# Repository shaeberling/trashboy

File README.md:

<p align="center">
  <em>A pocketable TRS-80 Model III/IV. Yes, really.</em>
</p>

## What is this?

A handheld **TRS-80 Model III / IV emulator** running on an ESP32-S3 board with a 640×480 RGB LCD.

It runs at original-hardware clock speed — 2.028 MHz for Model III, 4.055 MHz for Model IV — synchronised to wall-clock time so games play at their original speed. The 8 × 12 (M3) and 8 × 10 (M4) glyphs are blitted into an LVGL canvas with 90° rotation, so the portrait panel reads as a landscape Model III screen.

## Hardware

| Part | Role |
|------|------|
| **ESP32-S3** with 8 MB octal PSRAM | Runs the emulator, LVGL UI, BT, Wi-Fi, and a 16-bit RGB LCD bus simultaneously. |
| **ST7701S 480×640 RGB LCD** | Drawn as 640×480 landscape via software rotation in the LVGL flush callback. |
| **GT911 capacitive touch** | I²C; used for the boot-time input-test screen. |
| **TCA9554PWR I/O expander @ 0x20** | On-board: LCD CS, backlight enable, buzzer reset, etc. |
| **MCP23017 I/O expander @ 0x21** | Physical board buttons. Interrupt-driven via INTA → GPIO4. |
| **Bluetooth HID keyboard** | Any generic BT keyboard. Pairing persists in NVS. |
| **Buzzer** | LEDC PWM on GPIO 6 (shared with the LCD backlight channel). |

## Software stack

- **ESP-IDF** — Official ESP32 software stack
- **LVGL v9.1** in `LV_DISPLAY_RENDER_MODE_PARTIAL` with software rotation done inside the flush callback (the panel has no hardware rotation, and `lv_display_set_rotation` alone only swaps reported dimensions). An adaptive flush callback skips the rotation entirely when the emulator is running, since its TRSCanvas pre-rotates glyphs into an unrotated buffer.
- **libz80** Z80 emulation core in `components/ptrs/`, derived from `apuder/pTRS-80`.
- **RetroStore C SDK** (`components/retrostore-c-sdk/`, git submodule) for fetching downloadable game media. HTTP and decode buffers live in PSRAM to keep internal SRAM available for BT/Wi-Fi coexistence working memory.
- **esp-hid** wrapping BT Classic + BLE for the keyboard host.
- **TRS-IO / TRS-LIB** (`components/trs-io/`, `components/trs-lib/`) for on-screen menus, the F5 settings UI, and TRS-80 system I/O glue.

Want the full picture? See [`firmware/ARCHITECTURE.md`](firmware/ARCHITECTURE.md) — boot sequence, task layout, the rotation handoff between splash and emulator, memory placement rules, and lessons-learned annotations.

## Build & flash

```bash
# Once per shell session:
source ~/.espressif/tools/activate_idf_v6.0.1.sh

cd firmware
idf.py set-target esp32s3        # only the first time
idf.py build
idf.py -p /dev/ttyACM0 flash monitor
```

On WSL2, the USB device routing is its own little adventure — see [`firmware/wsl.md`](firmware/wsl.md).

## Repo layout

```
.
├── assets/         Artwork (logo PNGs)
└── firmware/       ESP-IDF project — the action lives here
    ├── main/         app_main, LVGL UI, splash, Wi-Fi setup,
    │                 RetroStore browser, MCP23017 buttons, input test
    ├── components/   Z80 core, TRS-80 emulator, BT keyboard,
    │                 RetroStore SDK, TRS-IO, TRS-LIB
    ├── scripts/      Serial logger, asset rotation helpers
    ├── ARCHITECTURE.md
    └── wsl.md
```

## Status

Active development on the `lvgl9` branch. Recent direction: ESP-IDF v6 migration, MCP23017 board buttons over IRQs, GT911 touch driver, RetroStore game launching with PSRAM-backed buffers, an adaptive flush callback for the LVGL pipeline.

---

<sub>Not affiliated with Tandy or Radio Shack. The TRS-80 trademark belongs to whoever owns it now.</sub>

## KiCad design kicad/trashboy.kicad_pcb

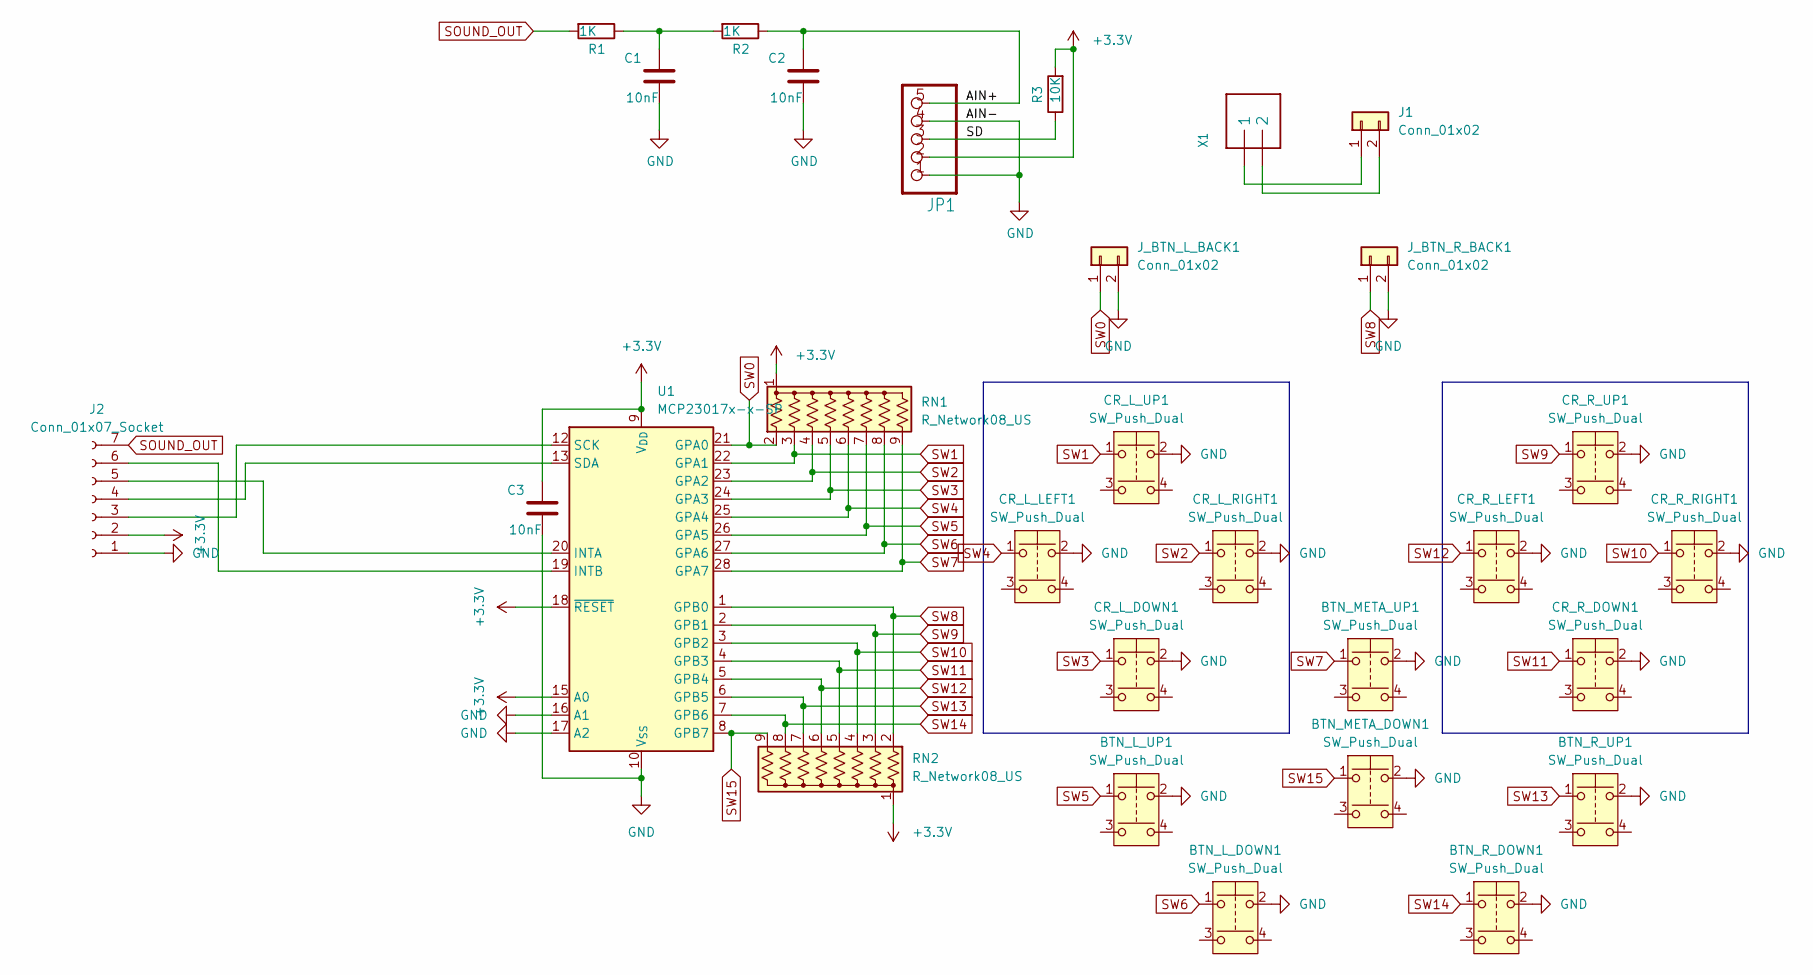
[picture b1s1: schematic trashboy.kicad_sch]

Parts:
BTN_L_DOWN1: SW_Push_Dual; SW_Push_Silicone_8x5mm
BTN_L_UP1: SW_Push_Dual; SW_Push_Silicone_8x5mm
BTN_META_DOWN1: SW_Push_Dual; SW_Push_Silicone_8x5mm
BTN_META_UP1: SW_Push_Dual; SW_Push_Silicone_8x5mm
BTN_R_DOWN1: SW_Push_Dual; SW_Push_Silicone_8x5mm
BTN_R_UP1: SW_Push_Dual; SW_Push_Silicone_8x5mm
C1, C2, C3: 10nF; C_0805_2012Metric_Pad1.18x1.45mm_HandSolder
CR_L_DOWN1: SW_Push_Dual; SW_Push_Silicone_8x5mm
CR_L_LEFT1: SW_Push_Dual; SW_Push_Silicone_8x5mm
CR_L_RIGHT1: SW_Push_Dual; SW_Push_Silicone_8x5mm
CR_L_UP1: SW_Push_Dual; SW_Push_Silicone_8x5mm
CR_R_DOWN1: SW_Push_Dual; SW_Push_Silicone_8x5mm
CR_R_LEFT1: SW_Push_Dual; SW_Push_Silicone_8x5mm
CR_R_RIGHT1: SW_Push_Dual; SW_Push_Silicone_8x5mm
CR_R_UP1: SW_Push_Dual; SW_Push_Silicone_8x5mm
J1: Conn_01x02; PinHeader_1x02_P2.54mm_Vertical
J2: Conn_01x07_Socket; PinHeader_1x07_P2.54mm_Vertical
JP1: HEADER-1X570MIL; 1X05_ROUND_70
J_BTN_L_BACK1: Conn_01x02; PinHeader_1x02_P2.54mm_Vertical
J_BTN_R_BACK1: Conn_01x02; PinHeader_1x02_P2.54mm_Vertical
R1, R2: 1K; R_0805_2012Metric_Pad1.20x1.40mm_HandSolder
R3: 10K; R_0805_2012Metric_Pad1.20x1.40mm_HandSolder
RN1, RN2: R_Network08_US; R_Array_SIP9
U1: MCP23017x-x-SP; DIP-28_W7.62mm
X1: TERMBLOCK_1X2; TERMBLOCK_1X2-3.5MM

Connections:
+3.3V: C3.1, J2.2, JP1.2, R3.2, RN1.1 (common), RN2.1 (common), U1.9 (V_{DD}), U1.15 (A0), U1.18 (~RESET)
/AIN+: C2.1, JP1.5, R2.1
/SD: JP1.3, R3.1
GND: BTN_L_DOWN1.2, BTN_L_UP1.2, BTN_META_DOWN1.2, BTN_META_UP1.2, BTN_R_DOWN1.2, BTN_R_UP1.2, C1.2, C2.2, C3.2, CR_L_DOWN1.2, CR_L_LEFT1.2, CR_L_RIGHT1.2, CR_L_UP1.2, CR_R_DOWN1.2, CR_R_LEFT1.2, CR_R_RIGHT1.2, CR_R_UP1.2, J2.1, JP1.1, JP1.4, J_BTN_L_BACK1.2, J_BTN_R_BACK1.2, U1.10 (V_{SS}), U1.16 (A1), U1.17 (A2)
unnamed: C1.1, R1.1, R2.2
unnamed: J1.1, X1.1
unnamed: J1.2, X1.2
unnamed: J2.3, U1.12 (SCK)
unnamed: J2.4, U1.13 (SDA)
unnamed: J2.5, U1.20 (INTA)
unnamed: J2.6, U1.19 (INTB)
SOUND_OUT: J2.7, R1.2
SW0: J_BTN_L_BACK1.1, RN1.2 (R1), U1.21 (GPA0)
SW1: CR_L_UP1.1, RN1.3 (R2), U1.22 (GPA1)
SW2: CR_L_RIGHT1.1, RN1.4 (R3), U1.23 (GPA2)
SW3: CR_L_DOWN1.1, RN1.5 (R4), U1.24 (GPA3)
SW4: CR_L_LEFT1.1, RN1.6 (R5), U1.25 (GPA4)
SW5: BTN_L_UP1.1, RN1.7 (R6), U1.26 (GPA5)
SW6: BTN_L_DOWN1.1, RN1.8 (R7), U1.27 (GPA6)
SW7: BTN_META_UP1.1, RN1.9 (R8), U1.28 (GPA7)
SW8: J_BTN_R_BACK1.1, RN2.2 (R1), U1.1 (GPB0)
SW9: CR_R_UP1.1, RN2.3 (R2), U1.2 (GPB1)
SW10: CR_R_RIGHT1.1, RN2.4 (R3), U1.3 (GPB2)
SW11: CR_R_DOWN1.1, RN2.5 (R4), U1.4 (GPB3)
SW12: CR_R_LEFT1.1, RN2.6 (R5), U1.5 (GPB4)
SW13: BTN_R_UP1.1, RN2.7 (R6), U1.6 (GPB5)
SW14: BTN_R_DOWN1.1, RN2.8 (R7), U1.7 (GPB6)
SW15: BTN_META_DOWN1.1, RN2.9 (R8), U1.8 (GPB7)

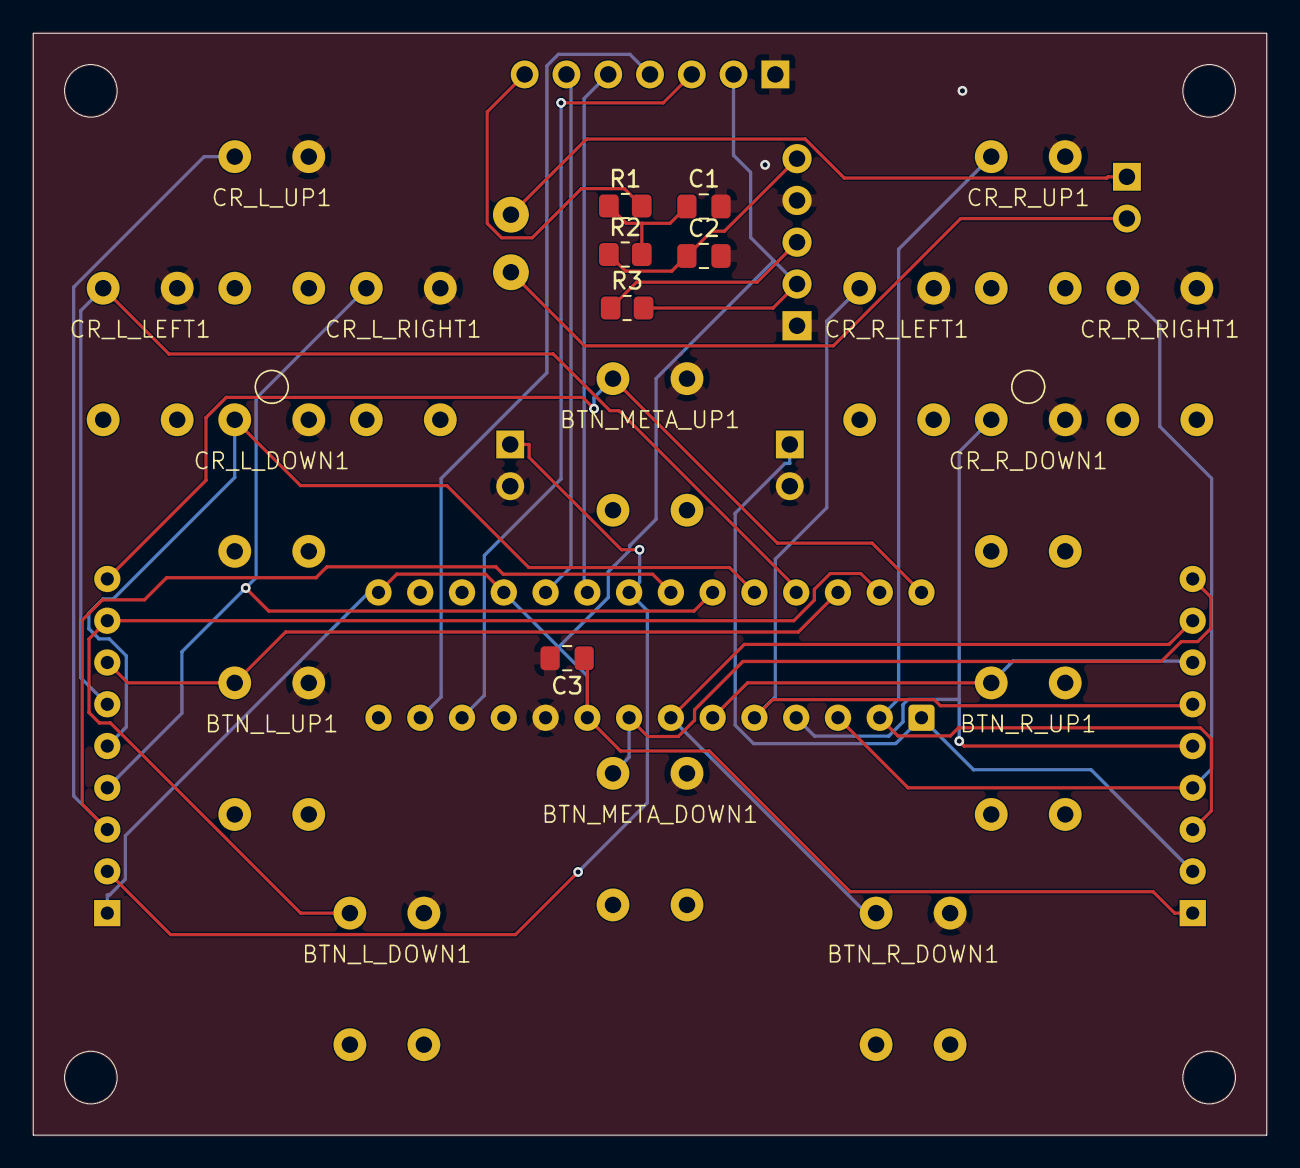
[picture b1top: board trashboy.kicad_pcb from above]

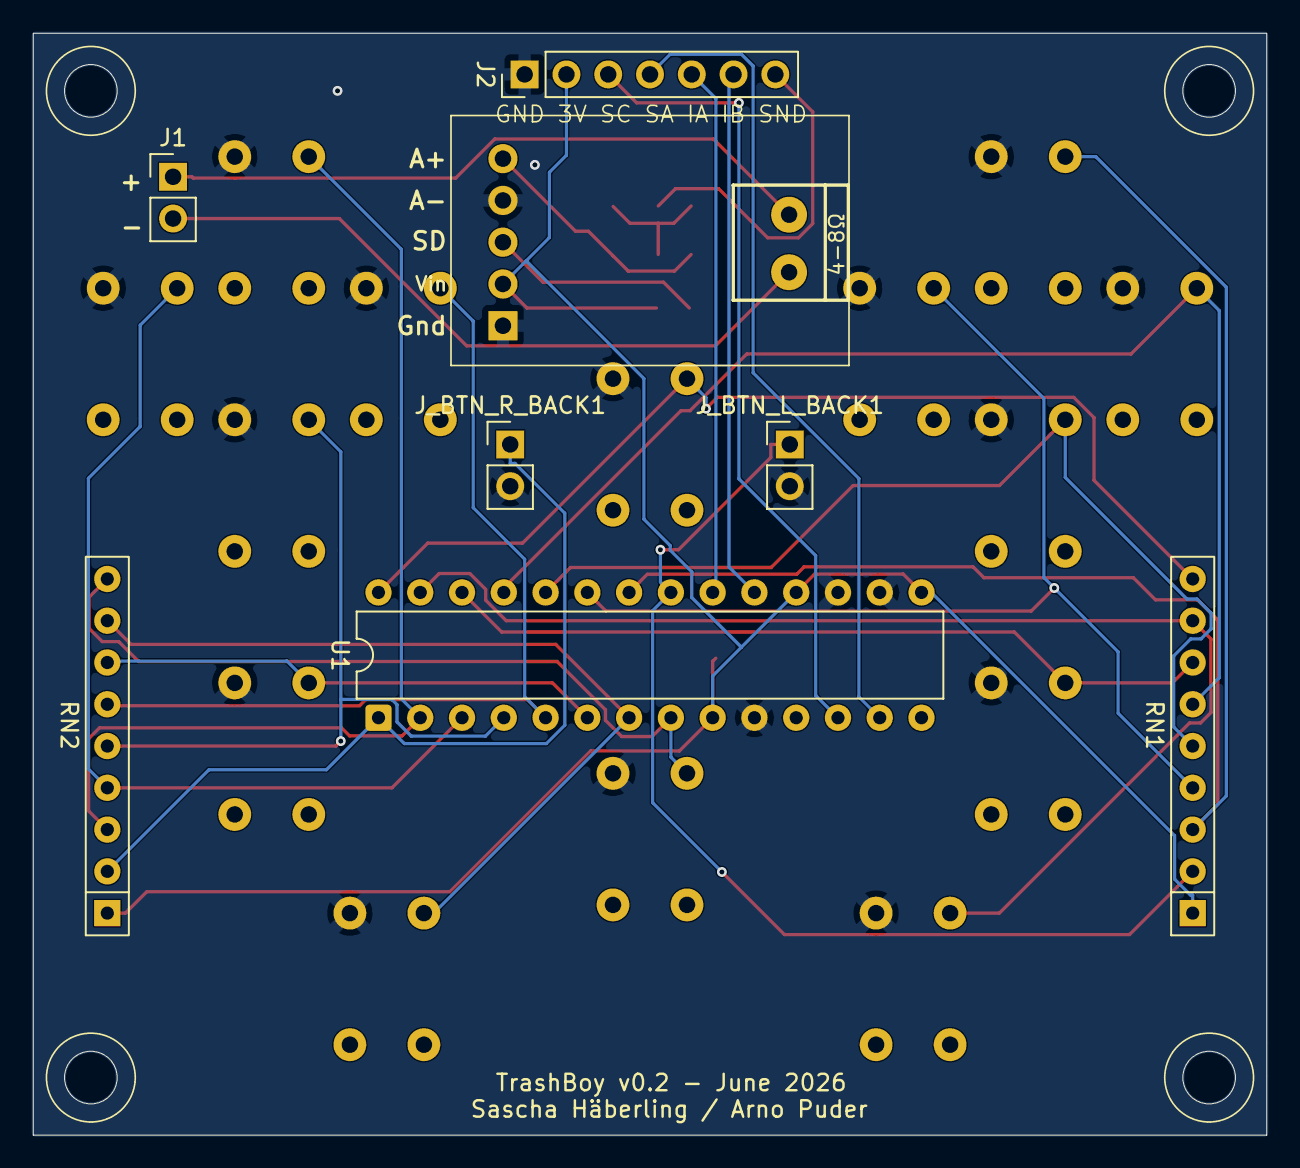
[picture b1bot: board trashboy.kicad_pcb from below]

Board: 2 copper layers, 75.0 x 67.0 mm, 29 parts (9 on the bottom side), 28 nets.

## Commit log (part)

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2026-02-05 Original demo
2026-02-05 Reduced to Hello World
2026-02-11 Update to LVGL v9
2026-02-13 Integrate COSMIC FIGHTER
2026-02-13 Move to folder firmware
2026-02-18 Working M3 display
2026-02-27 Working version of ptrs + BT
2026-05-14 Update `retrostore-c-sdk`
2026-05-14 Better support for Rii BT keyboard
2026-05-14 Support for sound
2026-05-28 KiCad schematics for sound
2026-06-16 Adding all of the component to the schematics.
2026-06-17 First attempt to place all the components, no traces yet.
2026-06-18 finished the PCB design and exported fabrication files.
